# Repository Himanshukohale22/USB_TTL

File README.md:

# USB_TTL
---
This repo contains the hardware files for USB-TTL programmer.this is open source project can be used and manufactured pcb. updating the project based on requirments.

Board specifications
--
* Programmer can be used for programming the microcontrollers .
* USB-B used for programming.
* can be connected to processing devices.
* jst connectors to Controllers.
* usb 5v converts to 3.3v.
* led indications for RX,TX and power.

PCB design
--
* Schematics

* 3D renders
  
  TOP

  BOTTOM

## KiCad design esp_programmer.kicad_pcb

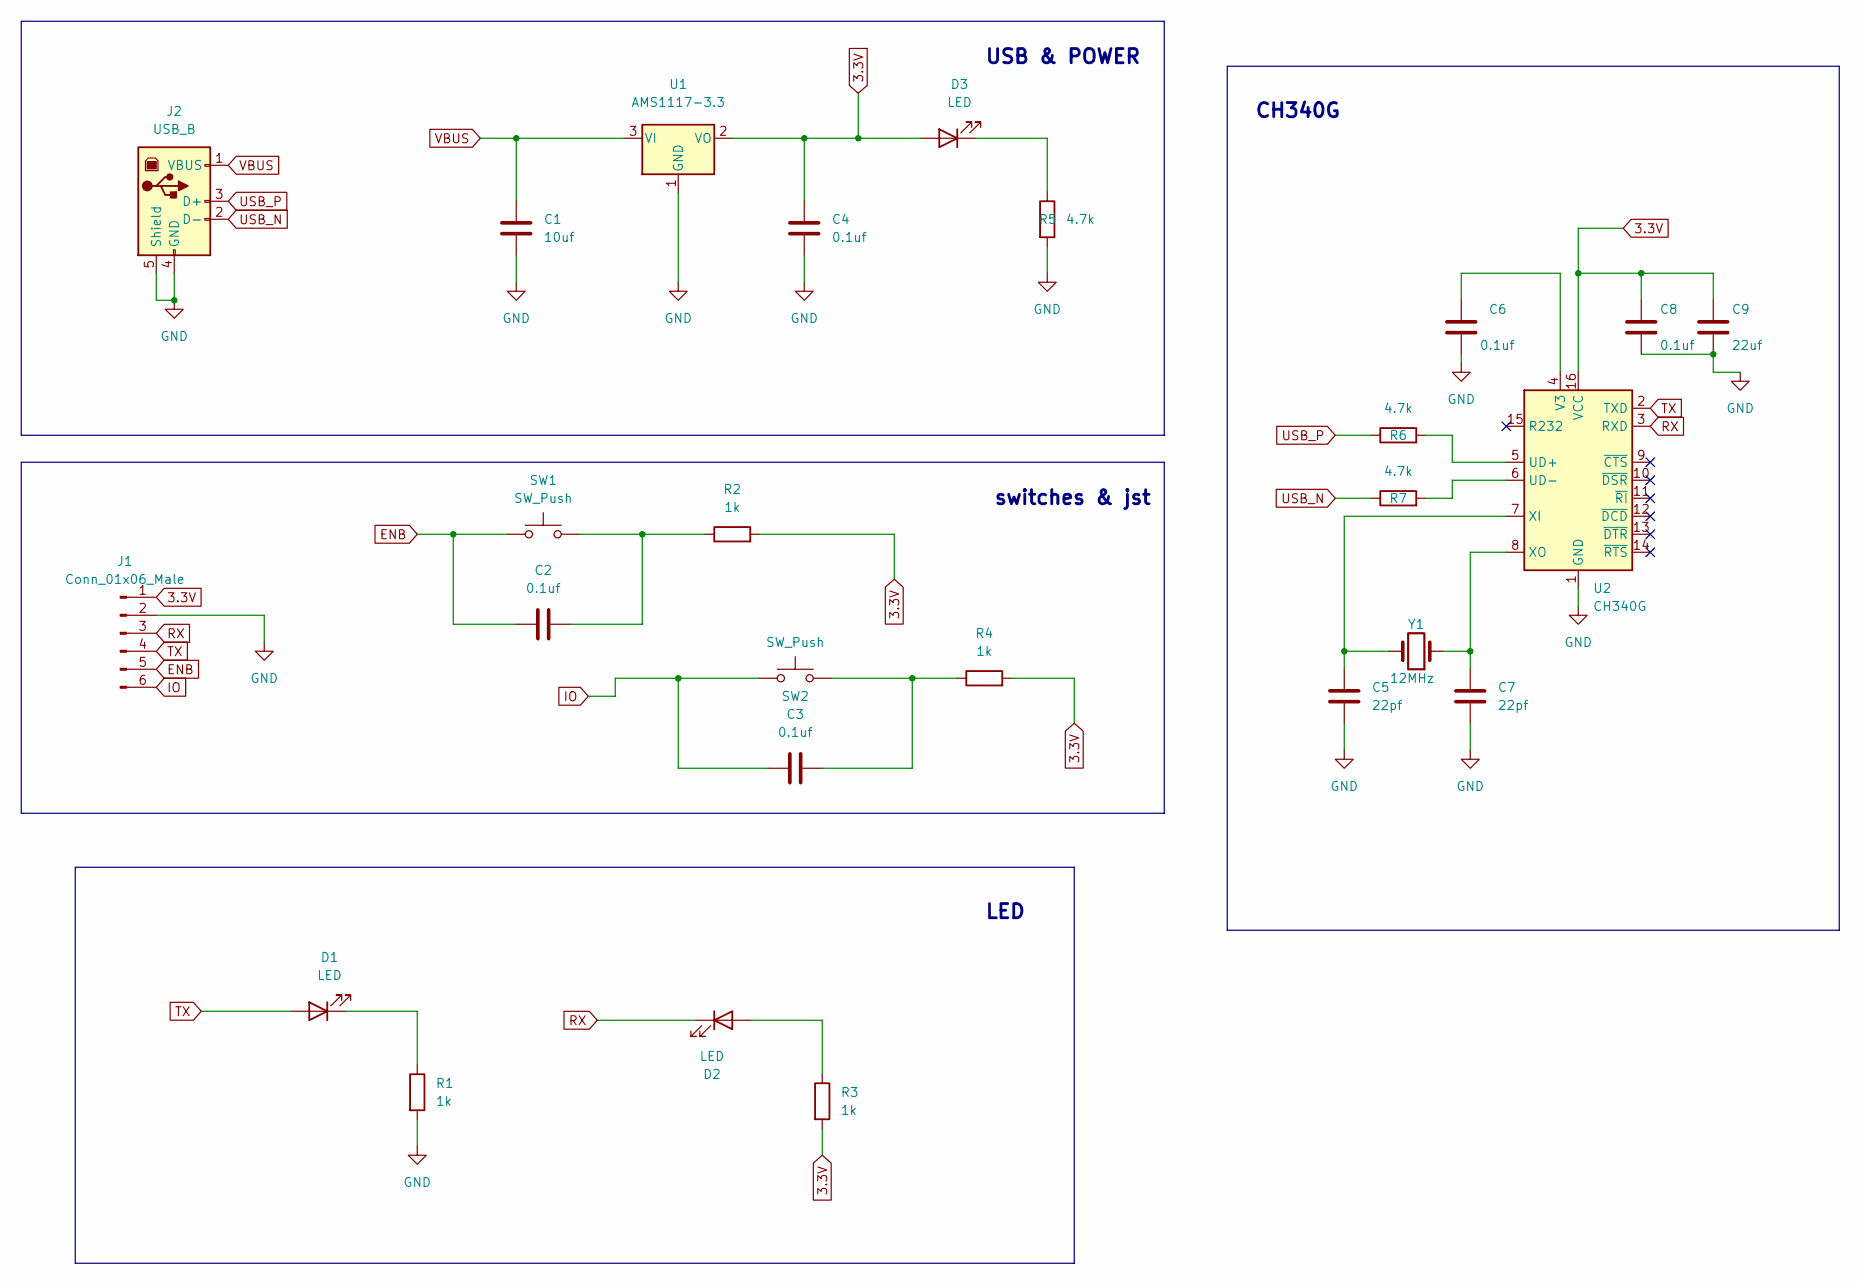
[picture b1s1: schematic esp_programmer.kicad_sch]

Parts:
C1: 10uf; C_0805_2012Metric_Pad1.18x1.45mm_HandSolder
C2, C3, C4, C6, C8: 0.1uf; C_0805_2012Metric_Pad1.18x1.45mm_HandSolder
C5, C7: 22pf; C_0805_2012Metric_Pad1.18x1.45mm_HandSolder
C9: 22uf; C_0805_2012Metric_Pad1.18x1.45mm_HandSolder
D1, D2, D3: LED; LED_0805_2012Metric_Pad1.15x1.40mm_HandSolder
J1: Conn_01x06_Male; JST_EH_B6B-EH-A_1x06_P2.50mm_Vertical
J2: USB_B; USB_B_OST_USB-B1HSxx_Horizontal
R1, R2, R3, R4: 1k; R_0805_2012Metric_Pad1.20x1.40mm_HandSolder
R5, R6, R7: 4.7k; R_0805_2012Metric_Pad1.20x1.40mm_HandSolder
SW1, SW2: SW_Push; SW_SPST_TL3342
U1: AMS1117-3.3; SOT-223-3_TabPin2
U2: CH340G; SOIC-16_3.9x9.9mm_P1.27mm
Y1: 12MHz; Crystal_HC18-U_Vertical

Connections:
3.3V: C4.1, C8.1, C9.1, D3.2 (A), J1.1, R2.2, R3.2, R4.2, U1.2 (VO), U2.16 (VCC)
ENB: C2.1, J1.5, SW1.1
GND: C1.2, C4.2, C5.2, C6.2, C7.2, C8.2, C9.2, J1.2, J2.4 (GND), J2.5 (Shield), R1.2, R5.2, U1.1 (GND), U2.1 (GND)
IO: C3.1, J1.6, SW2.1
unnamed: C2.2, R2.1, SW1.2
unnamed: C3.2, R4.1, SW2.2
unnamed: C5.1, U2.7 (XI), Y1.2
unnamed: C6.1, U2.4 (V3)
unnamed: C7.1, U2.8 (XO), Y1.1
unnamed: D1.1 (K), R1.1
unnamed: D2.2 (A), R3.1
unnamed: D3.1 (K), R5.1
unnamed: R6.2, U2.5 (UD+)
unnamed: R7.2, U2.6 (UD-)
RX: D2.1 (K), J1.3, U2.3 (RXD)
TX: D1.2 (A), J1.4, U2.2 (TXD)
USB_N: J2.2 (D-), R7.1
USB_P: J2.3 (D+), R6.1
VBUS: C1.1, J2.1 (VBUS), U1.3 (VI)

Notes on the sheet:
switches & jst
CH340G
LED
USB & POWER

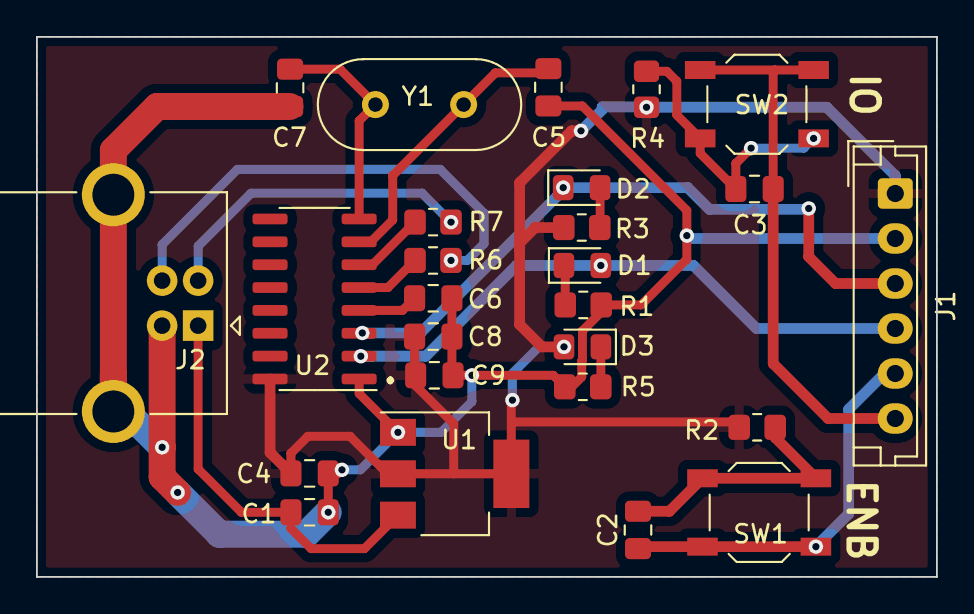
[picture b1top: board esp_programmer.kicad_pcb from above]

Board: 2 copper layers, 50.0 x 30.0 mm, 26 parts (0 on the bottom side), 19 nets.

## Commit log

2023-07-20 Adding Fp
2023-07-20 Create MIT LICENSE
2023-07-20 Adding Kicad files USB_TTL
